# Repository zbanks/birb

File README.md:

# birb
smol stack synthesizer for embedded systems, single-header, based on work by viznut et al.

# Running the demo

    $ make music

# Documentation

`birb` programs are arrays of values between `0x00` and `0x1F` (5 bits), terminated with `0xFF` (`BIRB_END`). 

Programs operate on a stack, making the programs very RPN-like. Popping a value from an empty stack yields `0`, and pushing a value onto a full stack overwrites the top value. The default maximum stack size is `64` but can be customized with `BIRB_STACK_SIZE`.

When evaluating programs, there is a special `T` value set which can be referenced from the birb program. This is intended to be used to produce time-varying output for synthesizing sounds.

After hitting the end of the program, top value on the stack is popped and returned from `birb_eval` (or `0` if the stack was empty).

## Opcode Reference

Most opcodes pop 2 values from the stack (`x` then `y`) and push a single value back:
- `BIRB_SHR`: `y >> x`
- `BIRB_SHL`: `y << x`
- `BIRB_AND`: `y & x`
- `BIRB_OR`: `y | x`
- `BIRB_XOR`: `y ^ x`
- `BIRB_ADD`: `y + x`
- `BIRB_SUB`: `y - x`
- `BIRB_MUL`: `y * x`
- `BIRB_DIV`: `y / x`, or `0` if `x == 0`
- `BIRB_MOD`: `y % x`, or `0` if `x == 0`
- `BIRB_DIG`: `(x << 4) | y`. Useful for constructing larger constants, e.g. `4 3 2 1 DIG DIG DIG` yields `0x1234`

Other opcodes that do not follow the above pattern:
- `0x0` - `0xF`: Push the given opcode onto the stack
- `BIRB_T`: Push the special variable `T` onto the stack
- `BIRB_U`: Push the special variable `U` onto the stack
- `BIRB_SWP`: Swap the position of the top two values on the stack
- `BIRB_DUP`: Duplicate the top value on the stack
- `BIRB_RND`: Pop `x` from the stack, then push `hash(x)` back

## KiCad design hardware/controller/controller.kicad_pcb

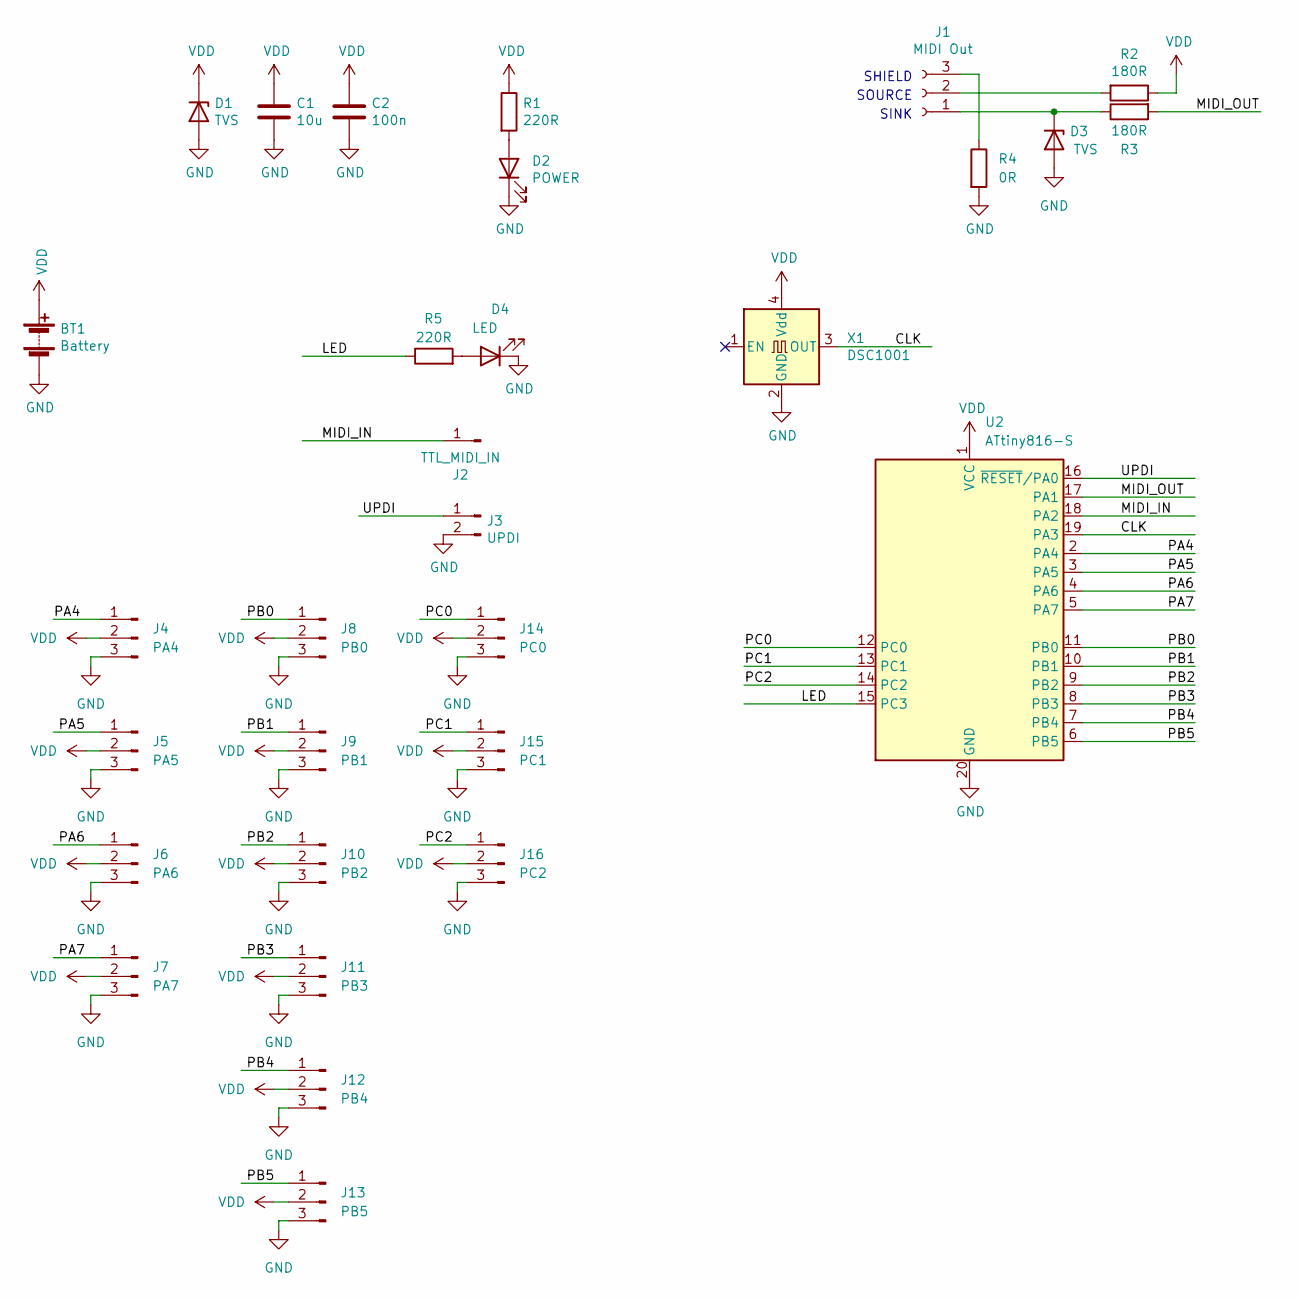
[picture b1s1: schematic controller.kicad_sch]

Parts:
BT1: Battery; PinHeader_1x02_P2.54mm_Vertical
C1: 10u; C_0805_2012Metric_Pad1.18x1.45mm_HandSolder
C2: 100n; C_0603_1608Metric_Pad1.08x0.95mm_HandSolder
D1, D3: TVS; SOD-323-handsoldering
D2: POWER; LED_D5.0mm
D4: LED; LED_D5.0mm
J1: MIDI Out; PinHeader_1x03_P2.54mm_Vertical
J2: TTL_MIDI_IN; PinHeader_1x01_P2.54mm_Vertical
J3: UPDI; PinHeader_1x02_P2.54mm_Vertical
J4: PA4; PinHeader_1x03_P2.54mm_Vertical
J5: PA5; PinHeader_1x03_P2.54mm_Vertical
J6: PA6; PinHeader_1x03_P2.54mm_Vertical
J7: PA7; PinHeader_1x03_P2.54mm_Vertical
J8: PB0; PinHeader_1x03_P2.54mm_Vertical
J9: PB1; PinHeader_1x03_P2.54mm_Vertical
J10: PB2; PinHeader_1x03_P2.54mm_Vertical
J11: PB3; PinHeader_1x03_P2.54mm_Vertical
J12: PB4; PinHeader_1x03_P2.54mm_Vertical
J13: PB5; PinHeader_1x03_P2.54mm_Vertical
J14: PC0; PinHeader_1x03_P2.54mm_Vertical
J15: PC1; PinHeader_1x03_P2.54mm_Vertical
J16: PC2; PinHeader_1x03_P2.54mm_Vertical
R1, R5: 220R; R_0603_1608Metric_Pad0.98x0.95mm_HandSolder
R2, R3: 180R; R_0603_1608Metric_Pad0.98x0.95mm_HandSolder
R4: 0R; R_0603_1608Metric_Pad0.98x0.95mm_HandSolder
U2: ATtiny816-S; SOIC-20W_7.5x12.8mm_P1.27mm
X1: DSC1001; DSC_1001_Oscillator_SMD_5032_4Pads

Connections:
/CLK: U2.19 (PA3), X1.3 (OUT)
/LED: R5.1, U2.15 (PC3)
/MIDI_IN: J2.1, U2.18 (PA2)
/MIDI_OUT: R3.2, U2.17 (PA1)
/PA4: J4.1, U2.2 (PA4)
/PA5: J5.1, U2.3 (PA5)
/PA6: J6.1, U2.4 (PA6)
/PA7: J7.1, U2.5 (PA7)
/PB0: J8.1, U2.11 (PB0)
/PB1: J9.1, U2.10 (PB1)
/PB2: J10.1, U2.9 (PB2)
/PB3: J11.1, U2.8 (PB3)
/PB4: J12.1, U2.7 (PB4)
/PB5: J13.1, U2.6 (PB5)
/PC0: J14.1, U2.12 (PC0)
/PC1: J15.1, U2.13 (PC1)
/PC2: J16.1, U2.14 (PC2)
/UPDI: J3.1, U2.16 (~RESET/PA0)
GND: BT1.2 (-), C1.2, C2.2, D1.2 (A), D2.1 (K), D3.2 (A), D4.1 (K), J3.2, J4.3, J5.3, J6.3, J7.3, J8.3, J9.3, J10.3, J11.3, J12.3, J13.3, J14.3, J15.3, J16.3, R4.2, U2.20 (GND), X1.2 (GND)
unnamed: D2.2 (A), R1.2
unnamed: D3.1 (K), J1.1, R3.1
unnamed: D4.2 (A), R5.2
unnamed: J1.2, R2.2
unnamed: J1.3, R4.1
VDD: BT1.1 (+), C1.1, C2.1, D1.1 (K), J4.2, J5.2, J6.2, J7.2, J8.2, J9.2, J10.2, J11.2, J12.2, J13.2, J14.2, J15.2, J16.2, R1.1, R2.1, U2.1 (VCC), X1.4 (Vdd)

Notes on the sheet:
SOURCE
SHIELD
SINK

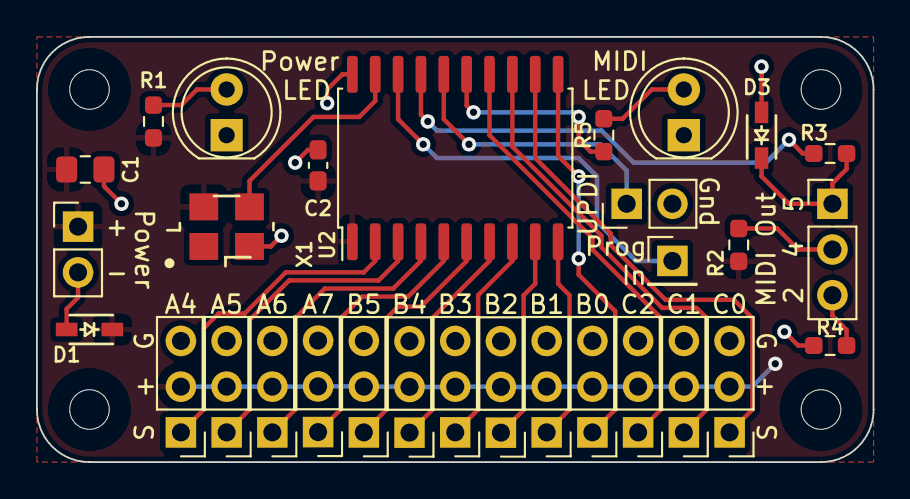
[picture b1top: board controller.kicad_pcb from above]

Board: 2 copper layers, 46.5 x 23.6 mm, 30 parts (0 on the bottom side), 25 nets.

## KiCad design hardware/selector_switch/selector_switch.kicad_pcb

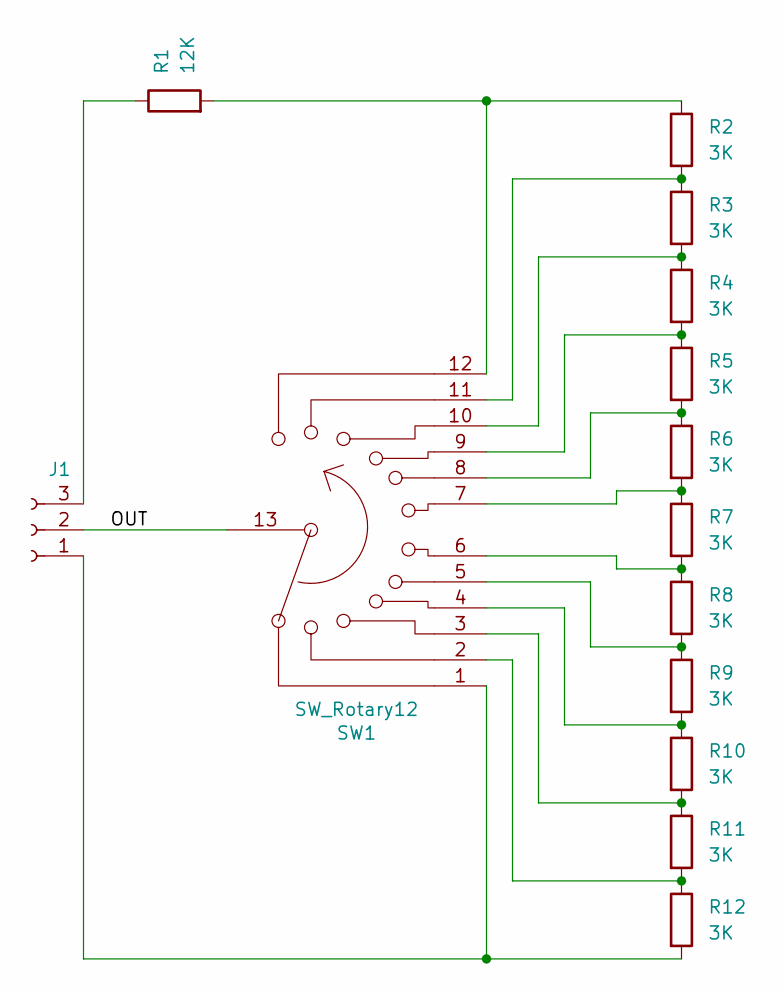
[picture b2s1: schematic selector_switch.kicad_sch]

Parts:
J1: Conn_01x03_Female; Pin_Header_Straight_1x03
R1: 12K; R_0603_1608Metric_Pad0.98x0.95mm_HandSolder
R2, R3, R4, R5, R6, R7, R8, R9, R10, R11, R12: 3K; R_0603_1608Metric_Pad0.98x0.95mm_HandSolder
SW1: SW_Rotary12; LORIN_12P1T

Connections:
/OUT: J1.2, SW1.13
unnamed: J1.1, R12.2, SW1.1
unnamed: J1.3, R1.1
unnamed: R1.2, R2.1, SW1.12
unnamed: R2.2, R3.1, SW1.11
unnamed: R3.2, R4.1, SW1.10
unnamed: R4.2, R5.1, SW1.9
unnamed: R5.2, R6.1, SW1.8
unnamed: R6.2, R7.1, SW1.7
unnamed: R7.2, R8.1, SW1.6
unnamed: R8.2, R9.1, SW1.5
unnamed: R9.2, R10.1, SW1.4
unnamed: R10.2, R11.1, SW1.3
unnamed: R11.2, R12.1, SW1.2

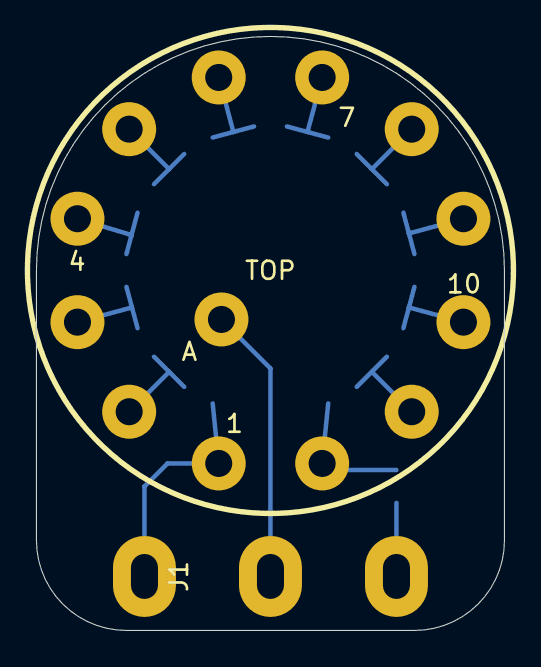
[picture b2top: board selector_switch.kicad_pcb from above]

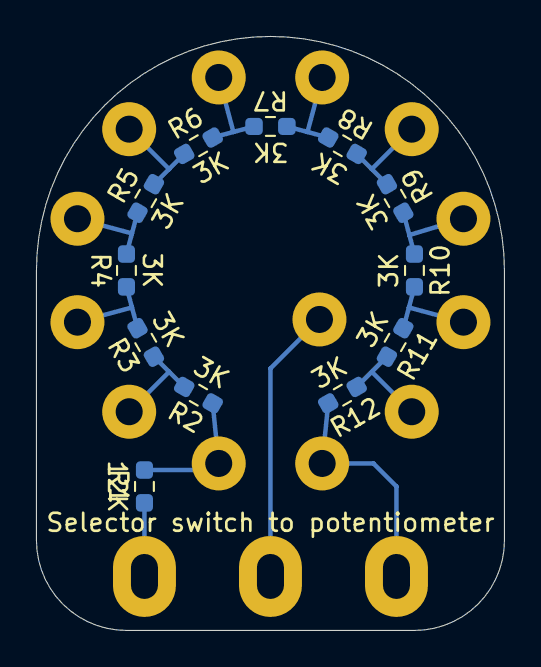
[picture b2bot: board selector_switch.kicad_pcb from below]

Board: 2 copper layers, 26.0 x 33.0 mm, 14 parts (12 on the bottom side), 14 nets.

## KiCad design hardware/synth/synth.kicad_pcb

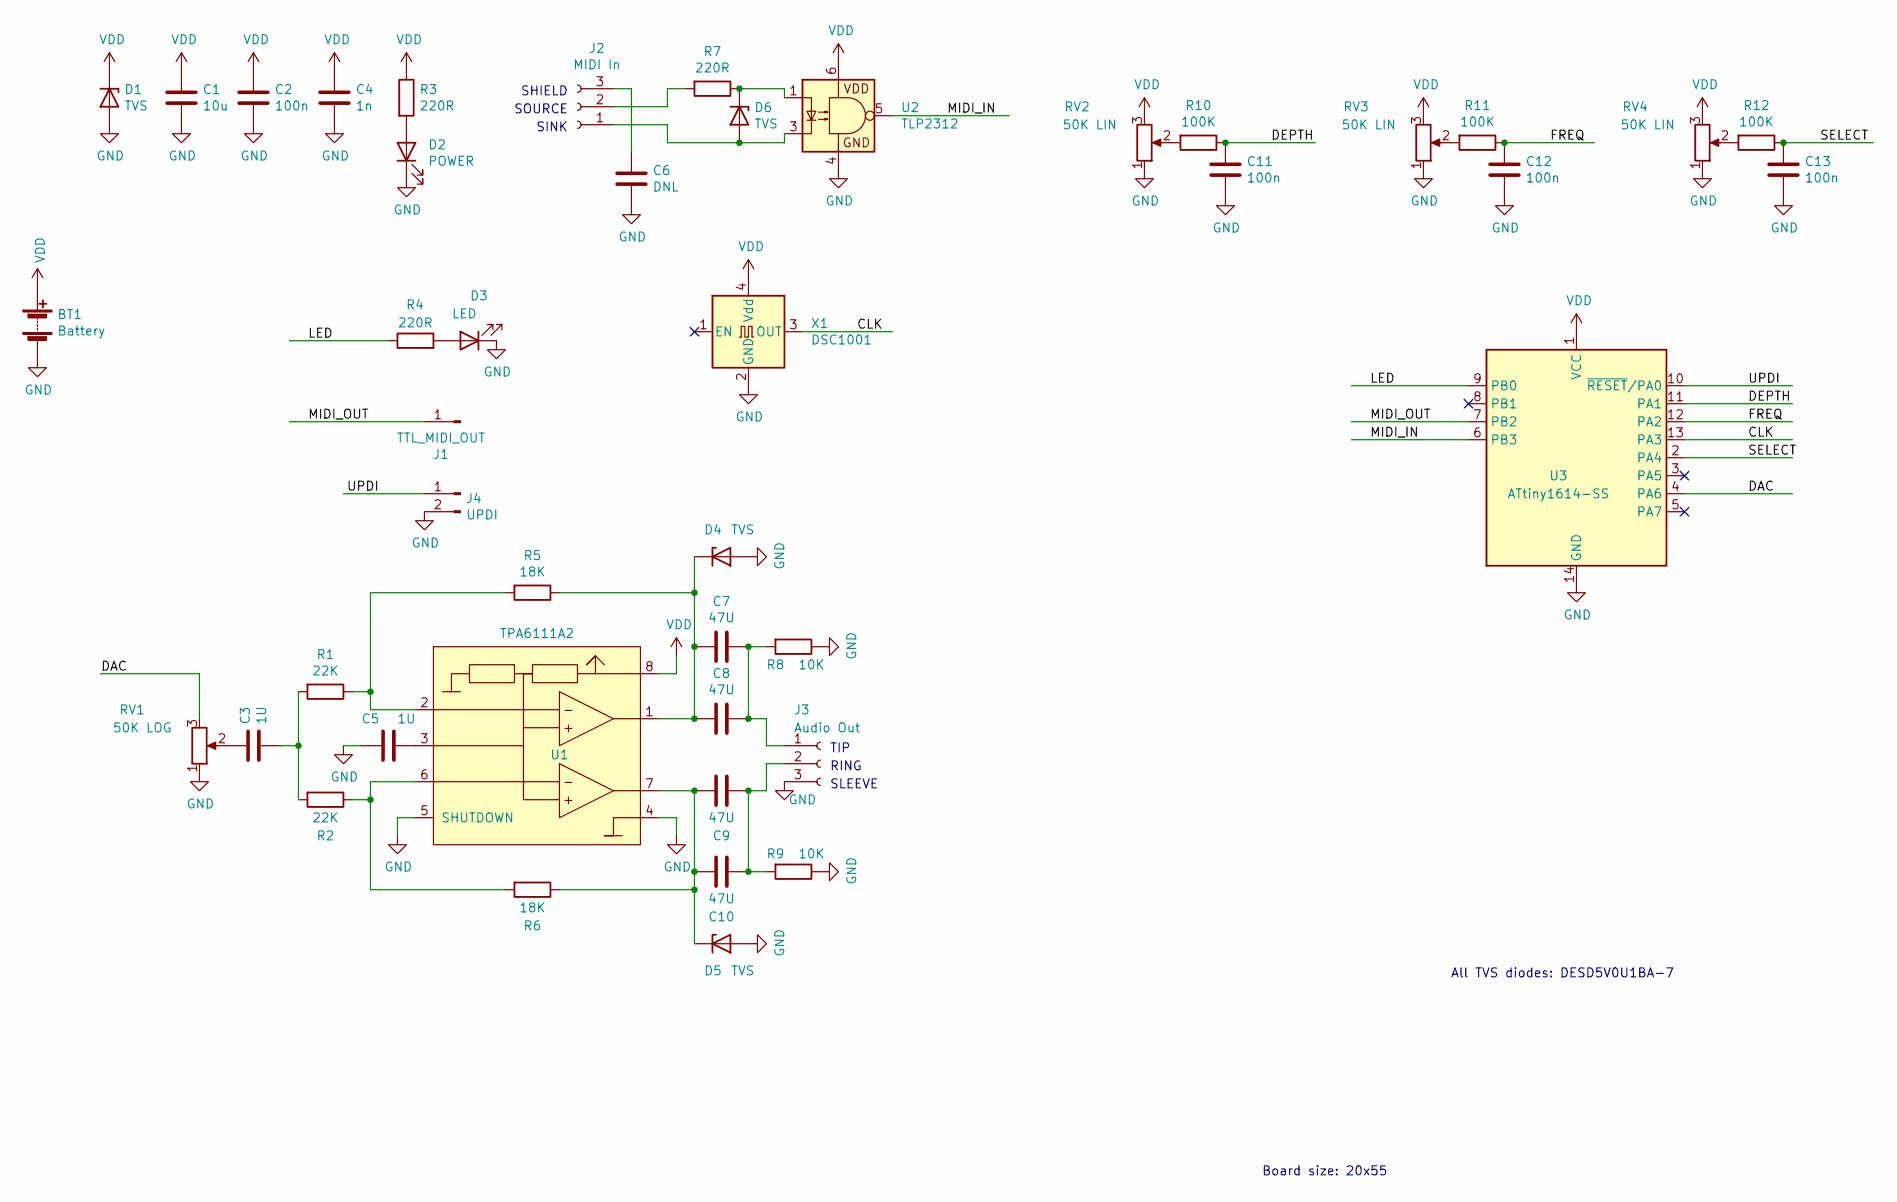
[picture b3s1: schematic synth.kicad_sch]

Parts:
BT1: Battery; Pin_Header_Straight_1x02
C1: 10u; C_0805_HandSoldering
C2, C11, C12, C13: 100n; C_0603_HandSoldering
C3, C5: 1U; C_0603_HandSoldering
C4: 1n; C_0603_HandSoldering
C6: DNL; C_0603_HandSoldering
C7, C8, C9, C10: 47U; C_1210_HandSoldering
D1, D4, D5, D6: TVS; SOD-323-handsoldering
D2: POWER; LED-5MM
D3: LED; LED-5MM
J1: TTL_MIDI_OUT; Pin_Header_Straight_1x01
J2: MIDI In; Pin_Header_Straight_1x03
J3: Audio Out; Pin_Header_Straight_1x03
J4: UPDI; Pin_Header_Straight_1x02
R1, R2: 22K; R_0603_HandSoldering
R3, R4, R7: 220R; R_0603_HandSoldering
R5, R6: 18K; R_0603_HandSoldering
R8, R9: 10K; R_0603_HandSoldering
R10, R11, R12: 100K; R_0603_HandSoldering
RV1: 50K LOG; Pin_Header_Straight_1x03
RV2, RV3, RV4: 50K LIN; Pin_Header_Straight_1x03
U1: TPA6111A2; SOIC-8-N
U2: TLP2312; SO-6_4.4x3.6mm_P1.27mm
U3: ATtiny1614-SS; SOIC-14_N
X1: DSC1001; DSC_1001_Oscillator_SMD_5032_4Pads

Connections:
/CLK: U3.13 (PA3), X1.3 (OUT)
/DAC: RV1.3, U3.4 (PA6)
/DEPTH: C11.1, R10.1, U3.11 (PA1)
/FREQ: C12.1, R11.1, U3.12 (PA2)
/LED: R4.1, U3.9 (PB0)
/MIDI_IN: U2.5, U3.6 (PB3)
/MIDI_OUT: J1.1, U3.7 (PB2)
/SELECT: C13.1, R12.1, U3.2 (PA4)
/UPDI: J4.1, U3.10 (~RESET/PA0)
GND: BT1.2 (-), C1.2, C2.2, C4.2, C5.1, C6.2, C11.2, C12.2, C13.2, D1.2 (A), D2.1 (K), D3.1 (K), D4.2 (A), D5.2 (A), J3.3, J4.2, R8.1, R9.1, RV1.1, RV2.1, RV3.1, RV4.1, U1.4 (GND), U1.5 (SHUTDOWN), U2.4, U3.14 (GND), X1.2 (GND)
unnamed: C3.1, RV1.2
unnamed: C5.2, U1.3 (BYPASS)
unnamed: C6.1, J2.3
unnamed: C7.1, C8.1, J3.1, R8.2
unnamed: C7.2, C8.2, D4.1 (K), R5.1, U1.1 (VO1)
unnamed: C9.1, C10.1, J3.2, R9.2
unnamed: C9.2, C10.2, D5.1 (K), R6.1, U1.7 (VO2)
unnamed: D2.2 (A), R3.2
unnamed: D3.2 (A), R4.2
unnamed: D6.1 (K), R7.1, U2.1
unnamed: D6.2 (A), J2.1, U2.3
unnamed: J2.2, R7.2
unnamed: R1.1, R5.2, U1.2 (IN1-)
unnamed: C3.2, R1.2, R2.2
unnamed: R2.1, R6.2, U1.6 (IN2-)
unnamed: R10.2, RV2.2
unnamed: R11.2, RV3.2
unnamed: R12.2, RV4.2
VDD: BT1.1 (+), C1.1, C2.1, C4.1, D1.1 (K), R3.1, RV2.3, RV3.3, RV4.3, U1.8 (VDD), U2.6, U3.1 (VCC), X1.4 (Vdd)

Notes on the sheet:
RING
Board size: 20x55
SINK
All TVS diodes: DESD5V0U1BA-7
SLEEVE
TIP
SOURCE
SHIELD

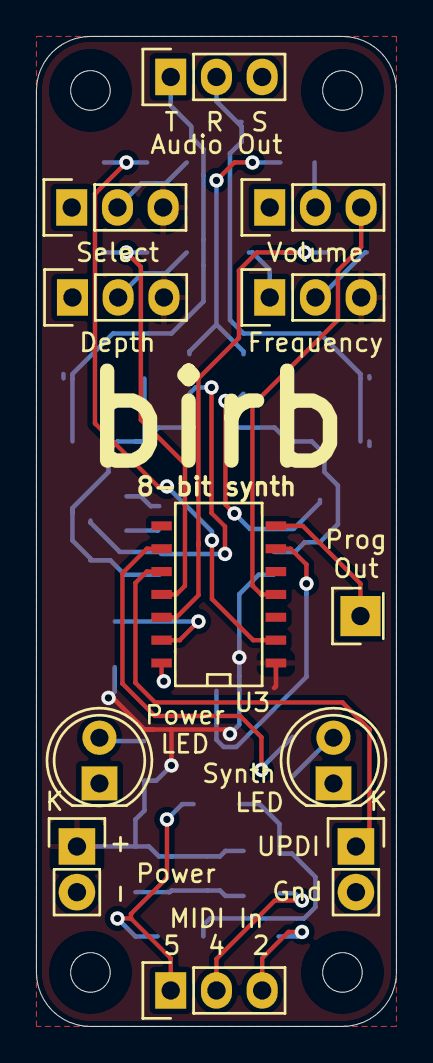
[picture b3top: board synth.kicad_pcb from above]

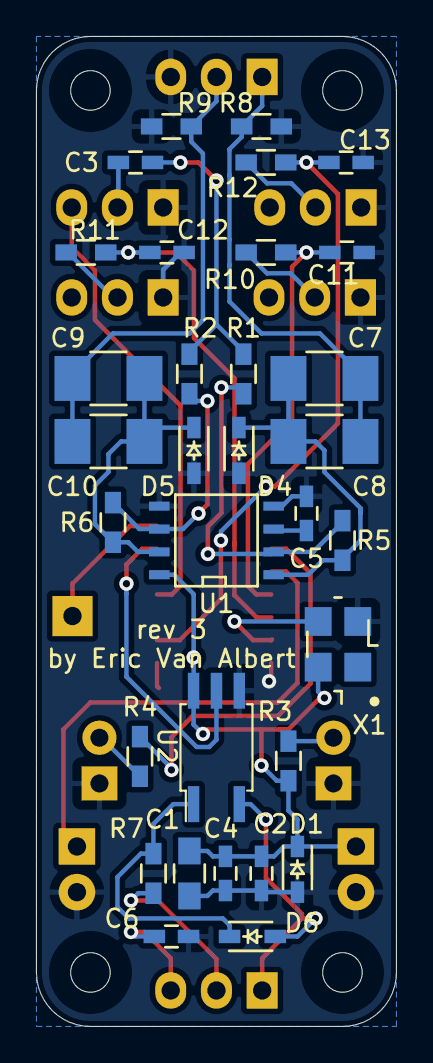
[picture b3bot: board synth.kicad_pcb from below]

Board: 2 copper layers, 20.0 x 55.0 mm, 44 parts (32 on the bottom side), 29 nets.

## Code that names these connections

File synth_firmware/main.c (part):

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    TCD0.CMPBCLR = 1250; // 8 KHz update rate
    TCD0.CTRLA |= TCD_ENABLE_bm;

    PORTB.DIRSET = 1 << 0; // Set PB0 as output

    VREF_CTRLA |= VREF_DAC0REFSEL_2V5_gc; // VREF = 2.5V for DAC
    VREF_CTRLB |= VREF_DAC0REFEN_bm; // Force enable VREF

    // Disable everything else on PA6
    PORTA.PIN6CTRL &= ~PORT_ISC_gm;
    PORTA.PIN6CTRL |= PORT_ISC_INPUT_DISABLE_gc;
    PORTA.PIN6CTRL &= ~PORT_PULLUPEN_bm;
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    ADC0.CTRLB |= ADC_PRESC_DIV8_gc; // 1.25MHz ADC clock rate
    ADC0.CTRLC |= ADC_REFSEL_VDDREF_gc; // Use full VDD for reference

    // Disable everything else on PA1
    PORTA.PIN1CTRL &= ~PORT_ISC_gm;
    PORTA.PIN1CTRL |= PORT_ISC_INPUT_DISABLE_gc;
    PORTA.PIN1CTRL &= ~PORT_PULLUPEN_bm;

    // Disable everything else on PA2
    PORTA.PIN2CTRL &= ~PORT_ISC_gm;
    PORTA.PIN2CTRL |= PORT_ISC_INPUT_DISABLE_gc;
    PORTA.PIN2CTRL &= ~PORT_PULLUPEN_bm;

    // Disable everything else on PA4
    PORTA.PIN4CTRL &= ~PORT_ISC_gm;
    PORTA.PIN4CTRL |= PORT_ISC_INPUT_DISABLE_gc;
    PORTA.PIN4CTRL &= ~PORT_PULLUPEN_bm;
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    ADC0.CTRLA |= ADC_ENABLE_bm; // Enable ADC

    // Enable UART TX and RX
    // Set PB2 as output
	PORTB.DIRSET = 1 << 2;

    // Invert PB3 input because this transceiver is weird
    PORTB.PIN3CTRL |= PORT_INVEN_bm;

    // Set PB3 pullup
    PORTB.PIN3CTRL |= PORT_PULLUPEN_bm;

    USART0.BAUD = 1280; // 31250 baud @ 10 MHz clock
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    static uint8_t last_depth;
    static uint8_t last_freq;

    ADC0.MUXPOS = ADC_MUXPOS_AIN1_gc; // Read from PA1
    ADC0.COMMAND |= ADC_STCONV_bm;
    while (ADC0.COMMAND & ADC_STCONV_bm);
    uint8_t read_depth = ADC0.RES >> 2;
    ADC0.MUXPOS = ADC_MUXPOS_AIN2_gc; // Read from PA2
    ADC0.COMMAND |= ADC_STCONV_bm;
    while (ADC0.COMMAND & ADC_STCONV_bm);
    uint8_t read_freq = ADC0.RES >> 2;
    ADC0.MUXPOS = ADC_MUXPOS_AIN4_gc; // Read from PA4
    ADC0.COMMAND |= ADC_STCONV_bm;
    while (ADC0.COMMAND & ADC_STCONV_bm);
    uint8_t read_select = ADC0.RES >> 6;
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
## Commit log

2019-06-15 Add more details to the README; Add the DUP operator
2019-06-17 Add SHL and second argument, reorder operators for easier keying in
2019-06-21 Add back DUP, add RND for white noise
2021-07-15 hardware birbs
2021-09-07 Add some preliminary synth firmware
2021-09-09 switch to a homogeneous increment scheme
2021-09-10 Get some ADSR and LFOs
2021-09-10 improve note triggering reliability
2021-09-10 Convert to sint8
2021-11-08 Fix some ADSR bugs, add pitch modulation, and remove obsolete code
2021-11-08 play around with some neat sounds
2021-11-13 Write MIDI bootloader
2021-11-13 Use bootloader by default when flashing chip, and shrink BL section to 2KB
2021-11-18 pad to 64 bytes
2021-11-18 Add longer reset delay so that flash gets written, and use mod wheel
2021-11-18 play with mod
2022-02-20 Add selector switch PCB
2022-03-09 Hardware rev 2 and some firmware updates
2022-03-10 detune testing
2022-03-10 rewrite, get detune sounding good
2022-03-12 2-voice polyphony
2022-03-13 Abstract oscillators
2022-03-13 3-voice polyphony
2022-03-13 add amplitude envelope generator
2022-03-13 add more EG and LFO
2022-03-13 play around with arp
2022-03-13 refactor into 'global' top-level object
2022-03-13 Start refactoring into patches
2022-03-13 Factor out arp
2022-03-14 Basic instrument working pretty well
2022-03-14 chorus patch
2022-03-15 Write third patch
2022-03-15 fix octave
2022-03-16 Add mono and octave modes, and move global LFOs to per-oscillator
2022-03-16 Bass starting to sound good
2022-03-17 reworking how notes are handled (WIP)
2022-03-17 get poly working with new 'held notes' strategy
2022-03-17 refactor note on/off slightly
2022-03-19 Octave and mono modes working
2022-03-19 Get glide working
2022-03-19 Add noise channel
2022-03-21 Optimize noise generator a little, fix some bugs
2022-03-21 Dirty bass
2022-03-24 Add pluck bass and fix some stuff
2022-03-25 Allow instruments to have different ranges
2022-03-25 basic bass sounding good
2022-03-26 start to work on percussion
2022-03-26 Percussion (with weird glitches)
2022-04-04 Start playing with DPCM
2022-04-04 Improve sample handling (needs a little more cleanup)
2022-04-04 Finish abstracting samples
2022-04-04 add 'bass' vocal
2022-05-19 Update synth board to rev3 (fixing volume control) and selector switch to rev2
2022-05-23 Add controller dev board
